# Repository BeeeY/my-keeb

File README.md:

# Beey's Keys
A custom 65% keyboard with a rotary encoder and oled screen. This was my first keyboard!

I made this since I needed a keyboard, and it just seemed really cool. It was kinda fun? I had some experience with kicad from making a hackpad, but this was definitely harder, especially since it was my second-ish hardware project. The rotary encoder and oled were particularly hard to figure out. Some parts were more enjoyable though, like cad, and in the end I'm really happy with the result. Especially the little bee, since I'm a Beey :3

## PCB

## Case

## Made With
-Kicad
-Omshape
-RMK

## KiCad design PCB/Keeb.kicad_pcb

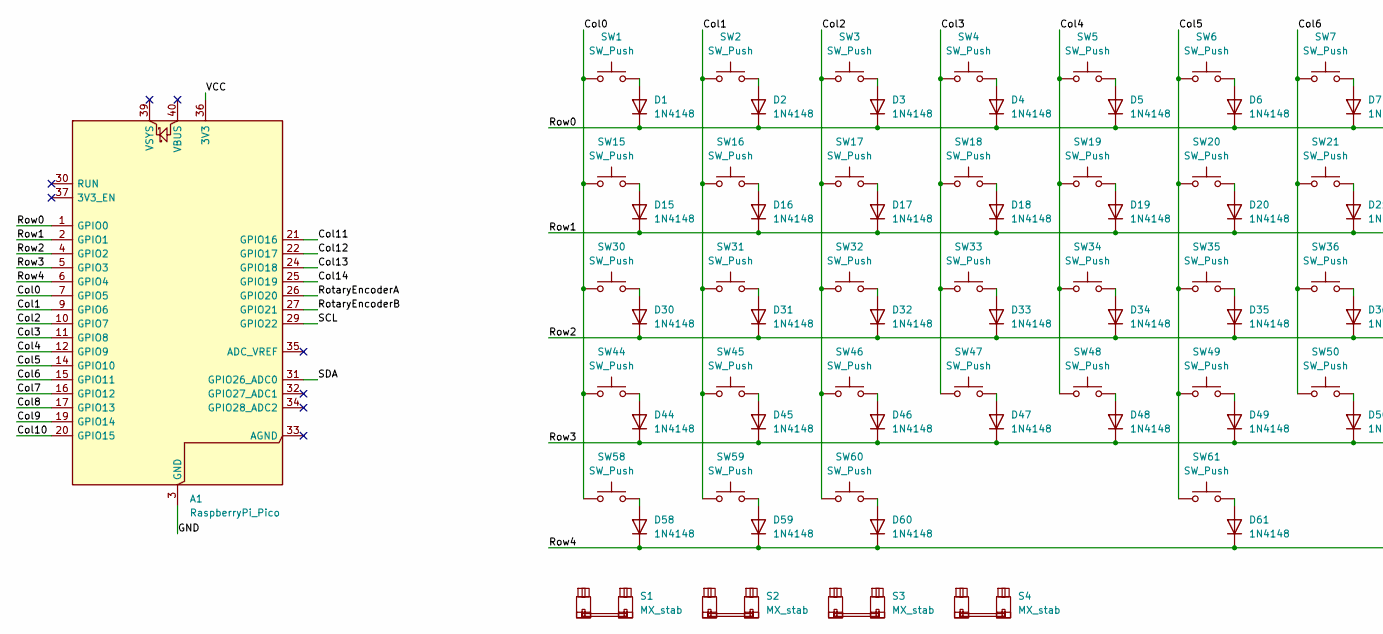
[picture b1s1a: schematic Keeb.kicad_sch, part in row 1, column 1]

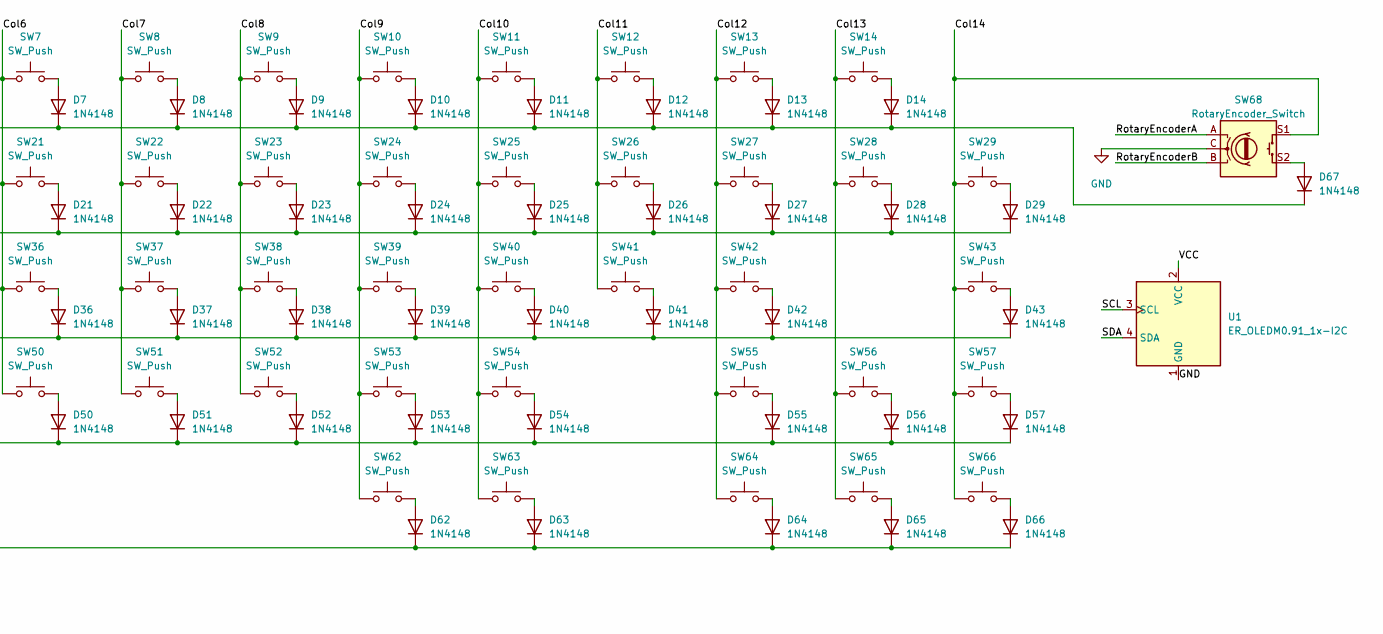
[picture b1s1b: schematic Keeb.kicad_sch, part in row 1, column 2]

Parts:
A1: RaspberryPi_Pico; RaspberryPi_Pico_Common_THT
D1, D2, D3, D4, D5, D6, D7, D8, D9, D10, D11, D12, D13, D14, D15, D16, D17, D18, D19, D20, D21, D22, D23, D24, D25, D26, D27, D28, D29, D30, D31, D32, D33, D34, D35, D36, D37, D38, D39, D40, D41, D42, D43, D44, D45, D46, D47, D48, D49, D50, D51, D52, D53, D54, D55, D56, D57, D58, D59, D60, D61, D62, D63, D64, D65, D66, D67: 1N4148; D_DO-35_SOD27_P7.62mm_Horizontal
S1: MX_stab; STAB_MX_6.25u
S2, S3: MX_stab; STAB_MX_2.25u
S4: MX_stab; STAB_MX_2u
SW1, SW2, SW3, SW4, SW5, SW6, SW7, SW8, SW9, SW10, SW11, SW12, SW13, SW14, SW15, SW16, SW17, SW18, SW19, SW20, SW21, SW22, SW23, SW24, SW25, SW26, SW27, SW28, SW29, SW30, SW31, SW32, SW33, SW34, SW35, SW36, SW37, SW38, SW39, SW40, SW41, SW42, SW43, SW44, SW45, SW46, SW47, SW48, SW49, SW50, SW51, SW52, SW53, SW54, SW55, SW56, SW57, SW58, SW59, SW60, SW61, SW62, SW63, SW64, SW65, SW66: SW_Push; SW_MX_1u
SW68: RotaryEncoder_Switch; ROT_Alps_EC11E-Switch
U1: ER_OLEDM0.91_1x-I2C

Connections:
/Col0: A1.7 (GPIO5), SW1.1, SW15.1, SW30.1, SW44.1, SW58.1
/Col1: A1.9 (GPIO6), SW2.1, SW16.1, SW31.1, SW45.1, SW59.1
/Col2: A1.10 (GPIO7), SW3.1, SW17.1, SW32.1, SW46.1, SW60.1
/Col3: A1.11 (GPIO8), SW4.1, SW18.1, SW33.1, SW47.1
/Col4: A1.12 (GPIO9), SW5.1, SW19.1, SW34.1, SW48.1
/Col5: A1.14 (GPIO10), SW6.1, SW20.1, SW35.1, SW49.1, SW61.1
/Col6: A1.15 (GPIO11), SW7.1, SW21.1, SW36.1, SW50.1
/Col7: A1.16 (GPIO12), SW8.1, SW22.1, SW37.1, SW51.1
/Col8: A1.17 (GPIO13), SW9.1, SW23.1, SW38.1, SW52.1
/Col9: A1.19 (GPIO14), SW10.1, SW24.1, SW39.1, SW53.1, SW62.1
/Col10: A1.20 (GPIO15), SW11.1, SW25.1, SW40.1, SW54.1, SW63.1
/Col11: A1.21 (GPIO16), SW12.1, SW26.1, SW41.1
/Col12: A1.22 (GPIO17), SW13.1, SW27.1, SW42.1, SW55.1, SW64.1
/Col13: A1.24 (GPIO18), SW14.1, SW28.1, SW56.1, SW65.1
/Col14: A1.25 (GPIO19), SW29.1, SW43.1, SW57.1, SW66.1, SW68.S1
/RotaryEncoderA: A1.26 (GPIO20), SW68.A
/RotaryEncoderB: A1.27 (GPIO21), SW68.B
/Row0: A1.1 (GPIO0), D1.1 (K), D2.1 (K), D3.1 (K), D4.1 (K), D5.1 (K), D6.1 (K), D7.1 (K), D8.1 (K), D9.1 (K), D10.1 (K), D11.1 (K), D12.1 (K), D13.1 (K), D14.1 (K), D67.1 (K)
/Row1: A1.2 (GPIO1), D15.1 (K), D16.1 (K), D17.1 (K), D18.1 (K), D19.1 (K), D20.1 (K), D21.1 (K), D22.1 (K), D23.1 (K), D24.1 (K), D25.1 (K), D26.1 (K), D27.1 (K), D28.1 (K), D29.1 (K)
/Row2: A1.4 (GPIO2), D30.1 (K), D31.1 (K), D32.1 (K), D33.1 (K), D34.1 (K), D35.1 (K), D36.1 (K), D37.1 (K), D38.1 (K), D39.1 (K), D40.1 (K), D41.1 (K), D42.1 (K), D43.1 (K)
/Row3: A1.5 (GPIO3), D44.1 (K), D45.1 (K), D46.1 (K), D47.1 (K), D48.1 (K), D49.1 (K), D50.1 (K), D51.1 (K), D52.1 (K), D53.1 (K), D54.1 (K), D55.1 (K), D56.1 (K), D57.1 (K)
/Row4: A1.6 (GPIO4), D58.1 (K), D59.1 (K), D60.1 (K), D61.1 (K), D62.1 (K), D63.1 (K), D64.1 (K), D65.1 (K), D66.1 (K)
/SCL: A1.29 (GPIO22), U1.3 (SCL)
/SDA: A1.31 (GPIO26_ADC0), U1.4 (SDA)
/VCC: A1.36 (3V3), U1.2 (VCC)
GND: A1.3 (GND), A1.8 (GND), A1.13 (GND), A1.18 (GND), A1.23 (GND), A1.28 (GND), A1.38 (GND), SW68.C, U1.1 (GND)
unnamed: D1.2 (A), SW1.2
unnamed: D2.2 (A), SW2.2
unnamed: D3.2 (A), SW3.2
unnamed: D4.2 (A), SW4.2
unnamed: D5.2 (A), SW5.2
unnamed: D6.2 (A), SW6.2
unnamed: D7.2 (A), SW7.2
unnamed: D8.2 (A), SW8.2
unnamed: D9.2 (A), SW9.2
unnamed: D10.2 (A), SW10.2
unnamed: D11.2 (A), SW11.2
unnamed: D12.2 (A), SW12.2
unnamed: D13.2 (A), SW13.2
unnamed: D14.2 (A), SW14.2
unnamed: D15.2 (A), SW15.2
unnamed: D16.2 (A), SW16.2
unnamed: D17.2 (A), SW17.2
unnamed: D18.2 (A), SW18.2
unnamed: D19.2 (A), SW19.2
unnamed: D20.2 (A), SW20.2
unnamed: D21.2 (A), SW21.2
unnamed: D22.2 (A), SW22.2
unnamed: D23.2 (A), SW23.2
unnamed: D24.2 (A), SW24.2
unnamed: D25.2 (A), SW25.2
unnamed: D26.2 (A), SW26.2
unnamed: D27.2 (A), SW27.2
unnamed: D28.2 (A), SW28.2
unnamed: D29.2 (A), SW29.2
unnamed: D30.2 (A), SW30.2
unnamed: D31.2 (A), SW31.2
unnamed: D32.2 (A), SW32.2
unnamed: D33.2 (A), SW33.2
unnamed: D34.2 (A), SW34.2
unnamed: D35.2 (A), SW35.2
unnamed: D36.2 (A), SW36.2
unnamed: D37.2 (A), SW37.2
unnamed: D38.2 (A), SW38.2
unnamed: D39.2 (A), SW39.2
unnamed: D40.2 (A), SW40.2
unnamed: D41.2 (A), SW41.2
unnamed: D42.2 (A), SW42.2
unnamed: D43.2 (A), SW43.2
unnamed: D44.2 (A), SW44.2
unnamed: D45.2 (A), SW45.2
unnamed: D46.2 (A), SW46.2
unnamed: D47.2 (A), SW47.2
unnamed: D48.2 (A), SW48.2
unnamed: D49.2 (A), SW49.2
unnamed: D50.2 (A), SW50.2
unnamed: D51.2 (A), SW51.2
unnamed: D52.2 (A), SW52.2
unnamed: D53.2 (A), SW53.2
unnamed: D54.2 (A), SW54.2
unnamed: D55.2 (A), SW55.2
unnamed: D56.2 (A), SW56.2
unnamed: D57.2 (A), SW57.2
unnamed: D58.2 (A), SW58.2
unnamed: D59.2 (A), SW59.2
unnamed: D60.2 (A), SW60.2
unnamed: D61.2 (A), SW61.2
unnamed: D62.2 (A), SW62.2
unnamed: D63.2 (A), SW63.2
unnamed: D64.2 (A), SW64.2
unnamed: D65.2 (A), SW65.2
unnamed: D66.2 (A), SW66.2
unnamed: D67.2 (A), SW68.S2

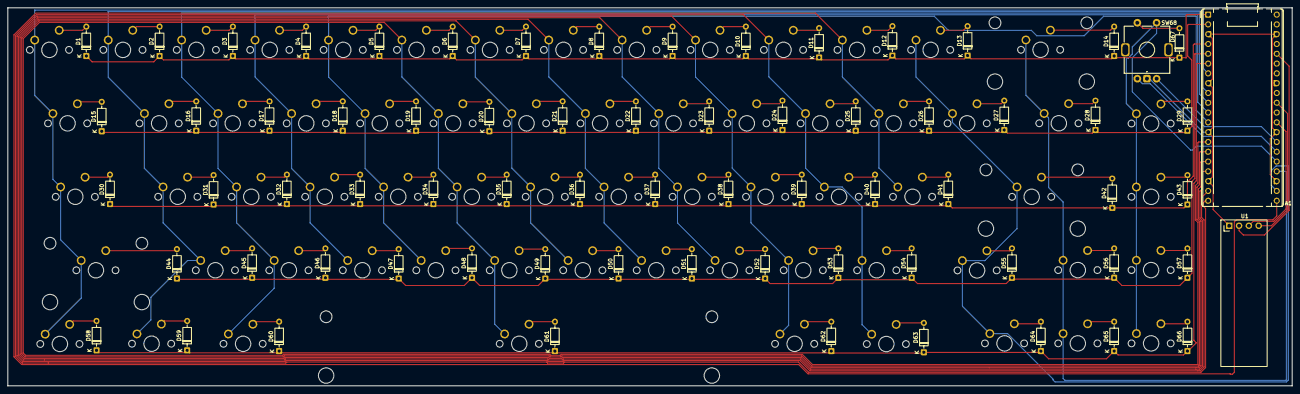
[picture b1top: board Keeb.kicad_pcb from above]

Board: 2 copper layers, 333.0 x 98.0 mm, 140 parts (0 on the bottom side), 93 nets.

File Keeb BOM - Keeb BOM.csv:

Reference,Qty,Value,DNP,Exclude from BOM,Exclude from Board,Footprint,Datasheet,Price (USD),Link
A1,1,RaspberryPi_Pico,,,,Module:RaspberryPi_Pico_Common_THT,https://datasheets.raspberrypi.com/pico/pico-datasheet.pdf,1.09,https://www.aliexpress.us/item/3256805430865417.html?spm=a2g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
"D1,D2,D3,D4,D5,D6,D7,D8,D9,D10,D11,D12,D13,D14,D15,D16,D17,D18,D19,D20,D21,D22,D23,D24,D25,D26,D27,D28,D29,D30,D31,D32,D33,D34,D35,D36,D37,D38,D39,D40,D41,D42,D43,D44,D45,D46,D47,D48,D49,D50,D51,D52,D53,D54,D55,D56,D57,D58,D59,D60,D61,D62,D63,D64,D65,D66,D67",67,1N4148,,,,Diode_THT:D_DO-35_SOD27_P7.62mm_Horizontal,https://assets.nexperia.com/documents/data-sheet/1N4148_1N4448.pdf,1.09,https://www.aliexpress.us/item/3256809192784213.html?spm=a2g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
S1,1,MX_stab,,,,PCM_marbastlib-mx:STAB_MX_6.25u,,,https://www.aliexpress.us/item/3256806342416791.html?spm=a2g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
"S2,S3",2,MX_stab,,,,PCM_marbastlib-mx:STAB_MX_2.25u,,,https://www.aliexpress.us/item/3256806342416791.html?spm=a2g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
S4,1,MX_stab,,,,PCM_marbastlib-mx:STAB_MX_2u,,1.09,https://www.aliexpress.us/item/3256806342416791.html?spm=a2g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
"SW1,SW2,SW3,SW4,SW5,SW6,SW7,SW8,SW9,SW10,SW11,SW12,SW13,SW14,SW15,SW16,SW17,SW18,SW19,SW20,SW21,SW22,SW23,SW24,SW25,SW26,SW27,SW28,SW29,SW30,SW31,SW32,SW33,SW34,SW35,SW36,SW37,SW38,SW39,SW40,SW41,SW42,SW43,SW44,SW45,SW46,SW47,SW48,SW49,SW50,SW51,SW52,SW53,SW54,SW55,SW56,SW57,SW58,SW59,SW60,SW61,SW62,SW63,SW64,SW65,SW66",66,SW_Push,,,,PCM_marbastlib-mx:SW_MX_1u,,9.39,https://www.aliexpress.us/item/3256807273323388.html?spm=a2g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
"SW1,SW2,SW3,SW4,SW5,SW6,SW7,SW8,SW9,SW10,SW11,SW12,SW13,SW14,SW15,SW16,SW17,SW18,SW19,SW20,SW21,SW22,SW23,SW24,SW25,SW26,SW27,SW28,SW29,SW30,SW31,SW32,SW33,SW34,SW35,SW36,SW37,SW38,SW39,SW40,SW41,SW42,SW43,SW44,SW45,SW46,SW47,SW48,SW49,SW50,SW51,SW52,SW53,SW54,SW55,SW56,SW57,SW58,SW59,SW60,SW61,SW62,SW63,SW64,SW65,SW66",66,SW Keys,,,,,,9.83,https://www.aliexpress.us/item/3256812711029094.html?spm=a2g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
SW68,1,RotaryEncoder_Switch,,,,PCM_marbastlib-various:ROT_Alps_EC11E-Switch,,1.09,https://www.aliexpress.us/item/3256813108230905.html?spm=a2g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
U1,1,ER_OLEDM0.91_1x-I2C,,,,Display:ER_OLEDM0.91_1x-I2C,https://www.buydisplay.com/download/manual/ER-OLEDM0.91-1_Da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,1.09,https://www.aliexpress.us/item/2251832650376908.html?gateway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
PCB,1,PCB,,,,,,55.63,
